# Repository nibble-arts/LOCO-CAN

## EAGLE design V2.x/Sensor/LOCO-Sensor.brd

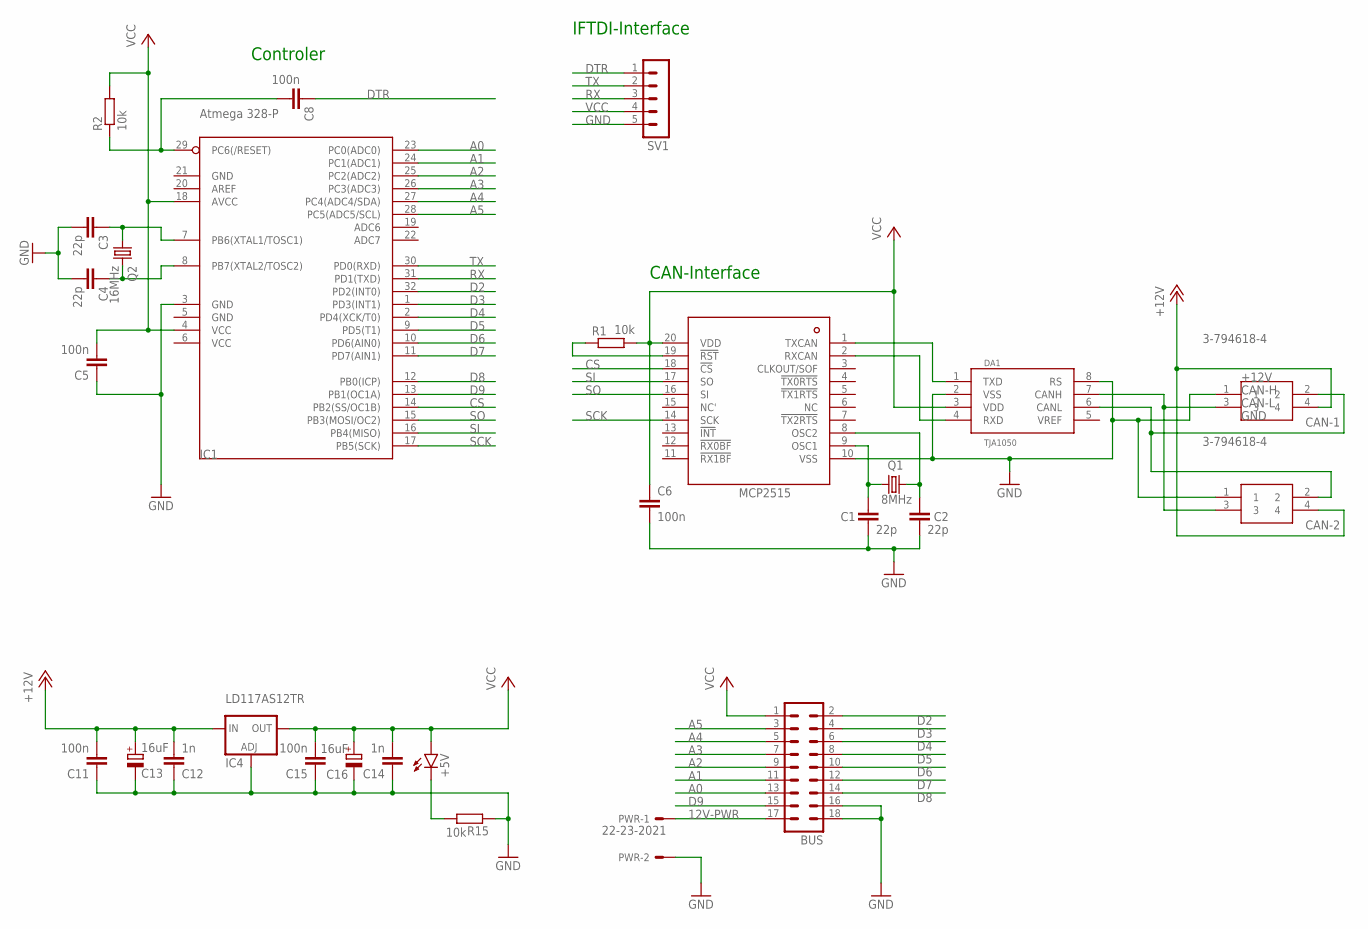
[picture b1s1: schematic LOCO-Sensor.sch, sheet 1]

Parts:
+5V: LEDCHIP-LED0603; CHIP-LED0603
BUS: MA09-2
C1, C2, C3, C4: 22p; C0402K
C5, C6, C8, C11, C15: 100n; C0402K
C12, C14: 1n; C0402K
C13, C16: 16uF; A/3216-18W
CAN-1, CAN-2: 3-794618-4; SHDRRA4W102P300_2X2_686X892X73
DA1: TJA1050; SO08
IC1: Atmega 328-P; TQFP32-08
IC2: MCP2515; TSSOP20
IC4: LD117AS12TR; SOT223
PWR: 22-23-2021
Q1: 8MHz; HC49/S
Q2: 16MHz; HC49/S
R1, R2, R15: 10k; MINI_MELF-0102W
SV1: MA05-1

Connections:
12V-PWR: BUS.17, PWR.1
+12V: C11.2, C12.2, C13.+, CAN-1.4, CAN-2.4, IC4.3 (IN)
A0: BUS.13, IC1.23 (PC0(ADC0))
A1: BUS.11, IC1.24 (PC1(ADC1))
A2: BUS.9, IC1.25 (PC2(ADC2))
A3: BUS.7, IC1.26 (PC3(ADC3))
A4: BUS.5, IC1.27 (PC4(ADC4/SDA))
A5: BUS.3, IC1.28 (PC5(ADC5/SCL))
CAN-H: CAN-1.3, CAN-2.3, DA1.7 (CANH)
CAN-L: CAN-1.2, CAN-2.2, DA1.6 (CANL)
CAN-OCC1: C1.1, IC2.9 (OSC1), Q1.1
CAN-OCC2: C2.1, IC2.8 (OSC2), Q1.2
CS: IC1.14 (PB2(SS/OC1B)), IC2.18 (!CS)
D2: BUS.2, IC1.32 (PD2(INT0))
D3: BUS.4, IC1.1 (PD3(INT1))
D4: BUS.6, IC1.2 (PD4(XCK/T0))
D5: BUS.8, IC1.9 (PD5(T1))
D6: BUS.10, IC1.10 (PD6(AIN0))
D7: BUS.12, IC1.11 (PD7(AIN1))
D8: BUS.14, IC1.12 (PB0(ICP))
D9: BUS.15, IC1.13 (PB1(OC1A))
DTR: C8.1, SV1.1
GND: BUS.16, BUS.18, C1.2, C2.2, C3.2, C4.2, C5.1, C6.2, C11.1, C12.1, C13.-, C14.1, C15.1, C16.-, CAN-1.1, CAN-2.1, DA1.2 (VSS), DA1.8 (RS), IC1.3 (GND), IC1.5 (GND), IC1.21 (GND), IC2.10 (VSS), IC4.1 (ADJ), PWR.2, R15.1, SV1.5
unnamed: IC2.19 (!RST), R1.1
unnamed: C3.1, IC1.7 (PB6(XTAL1/TOSC1)), Q2.1
unnamed: C4.1, IC1.8 (PB7(XTAL2/TOSC2)), Q2.2
unnamed: +5V.C, R15.2
unnamed: C8.2, IC1.29 (PC6(/RESET)), R2.1
RX: IC1.31 (PD1(TXD)), SV1.3
RXCAN: DA1.4 (RXD), IC2.2 (RXCAN)
SCK: IC1.17 (PB5(SCK)), IC2.14 (SCK)
SI: IC1.16 (PB4(MISO)), IC2.17 (SO)
SO: IC1.15 (PB3(MOSI/OC2)), IC2.16 (SI)
TX: IC1.30 (PD0(RXD)), SV1.2
TXCAN: DA1.1 (TXD), IC2.1 (TXCAN)
VCC: +5V.A, BUS.1, C5.2, C6.1, C14.2, C15.2, C16.+, DA1.3 (VDD), IC1.4 (VCC), IC1.6 (VCC), IC1.18 (AVCC), IC2.20 (VDD), IC4.4 (OUT), R1.2, R2.2, SV1.4

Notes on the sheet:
IFTDI-Interface
CAN-Interface
Controler

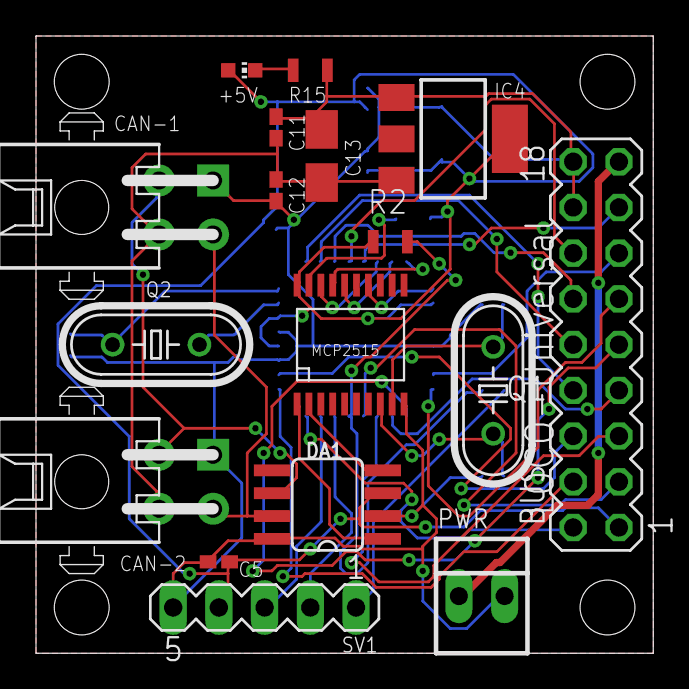
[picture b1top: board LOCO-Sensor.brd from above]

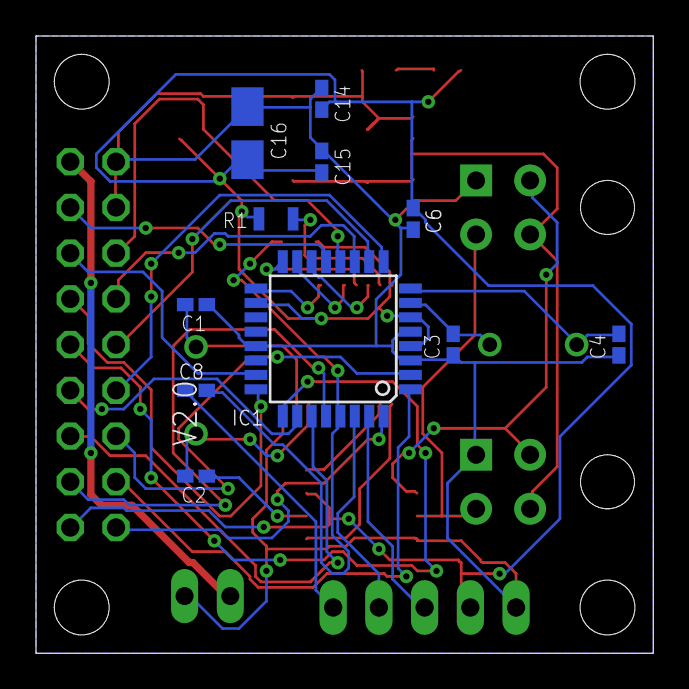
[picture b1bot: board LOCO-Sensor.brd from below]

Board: 2 copper layers, 34.3 x 34.3 mm, 28 parts (11 on the bottom side), 36 nets.

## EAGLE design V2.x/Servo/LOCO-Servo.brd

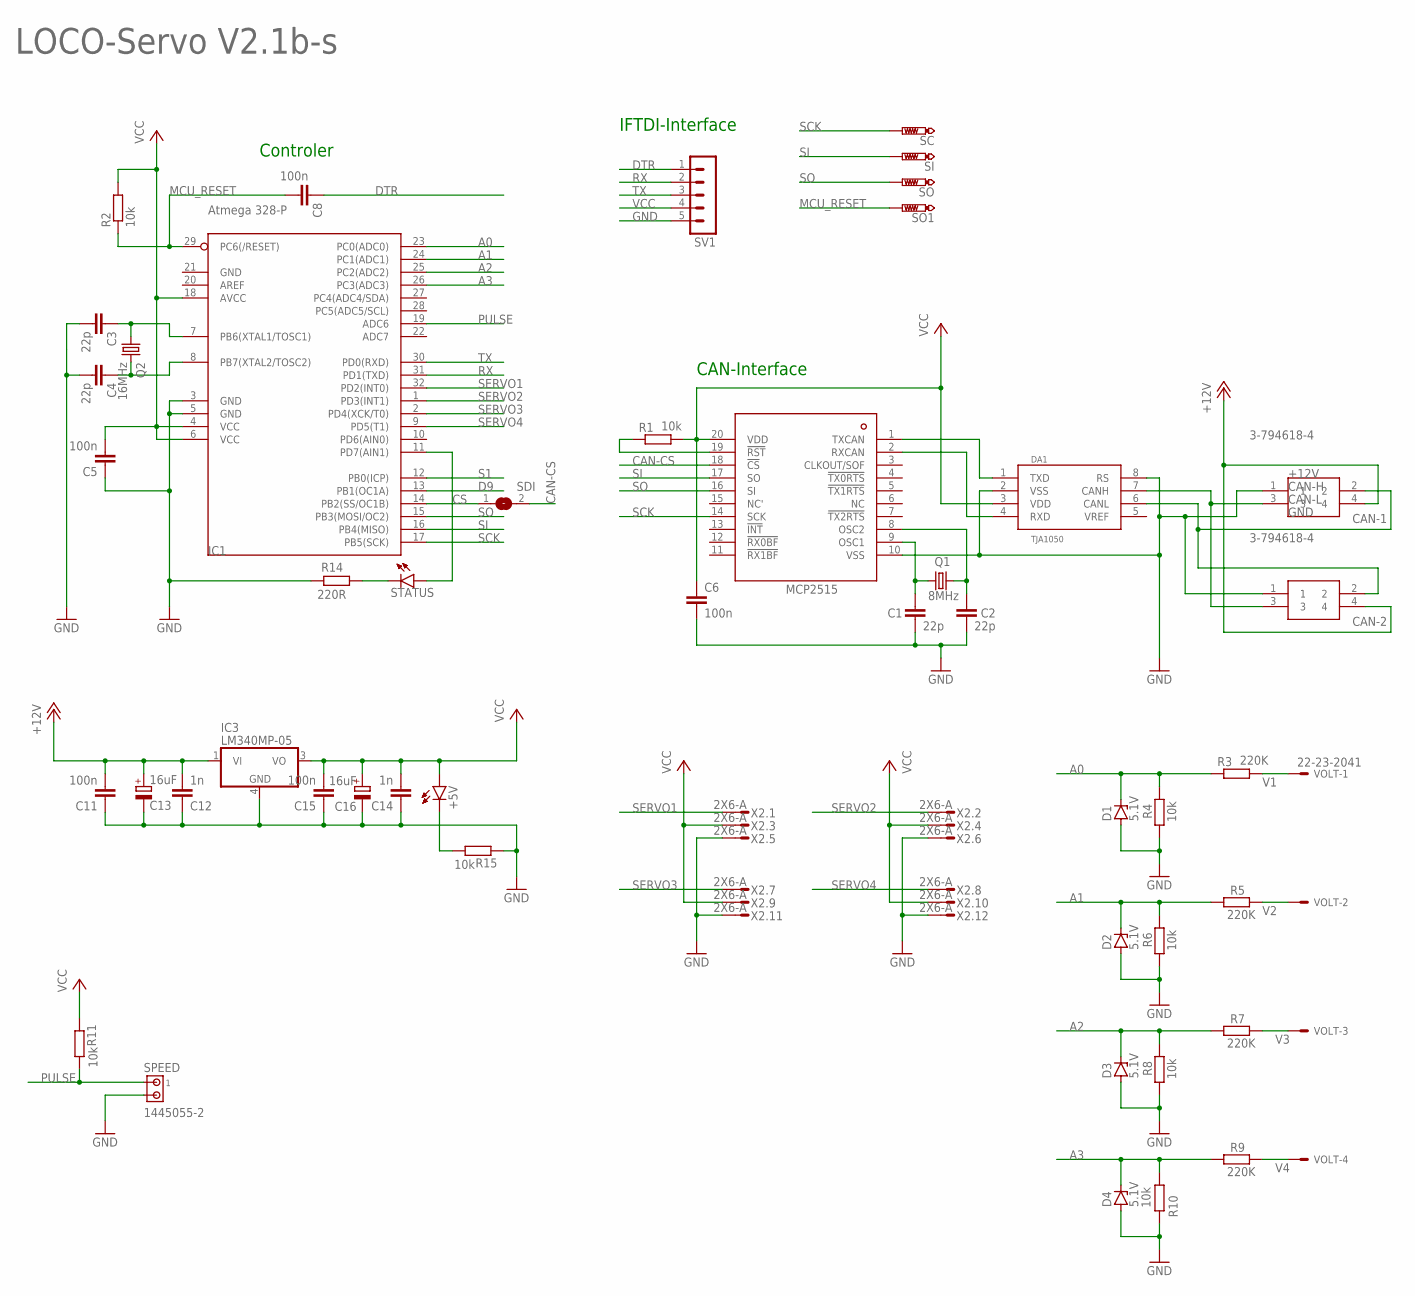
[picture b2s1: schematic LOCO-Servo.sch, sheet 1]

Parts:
+5V: LED_GREEN; LEDC1608X39N_G
C1, C2, C3, C4: 22p; C0402K
C5, C6, C8, C11, C15: 100n; C0402K
C12, C14: 1n; C0402K
C13, C16: 16uF; A/3216-18W
CAN: STATUS; LEDC1608X39N_B
CAN-1, CAN-2: 3-794618-4; SHDRRA4W102P300_2X2_686X892X73
D1, D2, D3, D4: 5.1V; SOD80C
DA1: TJA1050; SO08
IC1: Atmega 328-P; TQFP32-08
IC2: MCP2515; TSSOP20
IC3: LM340MP-05; SOT223
Q1: 8MHz; HC49/S
Q2: 16MHz; HC49/S
R1, R2, R4, R6, R8, R10, R11, R15: 10k; MINI_MELF-0102W
R3, R5, R7, R9: 220K; MINI_MELF-0102W
R14: 220R; MINI_MELF-0102W
SC: PTR1B1,27; B1,27
SDI: SJ
SI: PTR1B1,27; B1,27
SO, SO1: PTR1B1,27; B1,27
SPEED: 1445055-2
SV1: MA05-1
VOLT: 22-23-2041
X2: 2X6-A; 4-794618-2

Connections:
+12V: C11.2, C12.2, C13.+, CAN-1.4, CAN-2.4, IC3.1 (VI)
A0: D1.C, IC1.23 (PC0(ADC0)), R3.1, R4.2
A1: D2.C, IC1.24 (PC1(ADC1)), R5.1, R6.2
A2: D3.C, IC1.25 (PC2(ADC2)), R7.1, R8.2
A3: D4.C, IC1.26 (PC3(ADC3)), R9.1, R10.2
CAN-CS: IC2.18 (!CS), SDI.2
CAN-H: CAN-1.3, CAN-2.3, DA1.7 (CANH)
CAN-L: CAN-1.2, CAN-2.2, DA1.6 (CANL)
CAN-OCC1: C1.1, IC2.9 (OSC1), Q1.1
CAN-OCC2: C2.1, IC2.8 (OSC2), Q1.2
CS: IC1.14 (PB2(SS/OC1B)), SDI.1
D9: IC1.13 (PB1(OC1A))
DTR: C8.1, SV1.1
GND: C1.2, C2.2, C3.2, C4.2, C5.1, C6.2, C11.1, C12.1, C13.-, C14.1, C15.1, C16.-, CAN-1.1, CAN-2.1, D1.A, D2.A, D3.A, D4.A, DA1.2 (VSS), DA1.8 (RS), IC1.3 (GND), IC1.5 (GND), IC1.21 (GND), IC2.10 (VSS), IC3.4 (GND), R4.1, R6.1, R8.1, R10.1, R14.2, R15.1, SPEED.2, SV1.5, X2.5, X2.6, X2.11, X2.12
MCU_RESET: C8.2, IC1.29 (PC6(/RESET)), R2.1, SO1.TP
unnamed: CAN.1 (C), R14.1
unnamed: CAN.2 (A), IC1.11 (PD7(AIN1))
unnamed: IC2.19 (!RST), R1.1
unnamed: C3.1, IC1.7 (PB6(XTAL1/TOSC1)), Q2.1
unnamed: C4.1, IC1.8 (PB7(XTAL2/TOSC2)), Q2.2
unnamed: +5V.1 (C), R15.2
PULSE: IC1.19 (ADC6), R11.2, SPEED.1
RX: IC1.31 (PD1(TXD)), SV1.2
RXCAN: DA1.4 (RXD), IC2.2 (RXCAN)
S1: IC1.12 (PB0(ICP))
SCK: IC1.17 (PB5(SCK)), IC2.14 (SCK), SC.TP
SERVO1: IC1.32 (PD2(INT0)), X2.1
SERVO2: IC1.1 (PD3(INT1)), X2.2
SERVO3: IC1.2 (PD4(XCK/T0)), X2.7
SERVO4: IC1.9 (PD5(T1)), X2.8
SI: IC1.16 (PB4(MISO)), IC2.17 (SO), SI.TP
SO: IC1.15 (PB3(MOSI/OC2)), IC2.16 (SI), SO.TP
TX: IC1.30 (PD0(RXD)), SV1.3
TXCAN: DA1.1 (TXD), IC2.1 (TXCAN)
V1: R3.2, VOLT.1
V2: R5.2, VOLT.2
V3: R7.2, VOLT.3
V4: R9.2, VOLT.4
VCC: +5V.2 (A), C5.2, C6.1, C14.2, C15.2, C16.+, DA1.3 (VDD), IC1.4 (VCC), IC1.6 (VCC), IC1.18 (AVCC), IC2.20 (VDD), IC3.3 (VO), R1.2, R2.2, R11.1, SV1.4, X2.3, X2.4, X2.9, X2.10

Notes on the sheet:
IFTDI-Interface
CAN-Interface
Controler
LOCO-Servo V2.1b-s

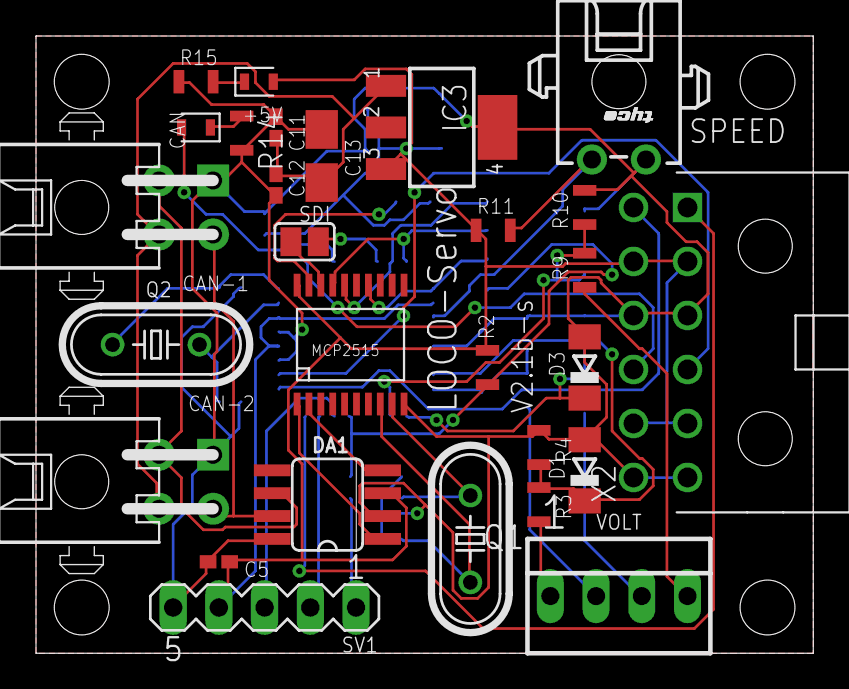
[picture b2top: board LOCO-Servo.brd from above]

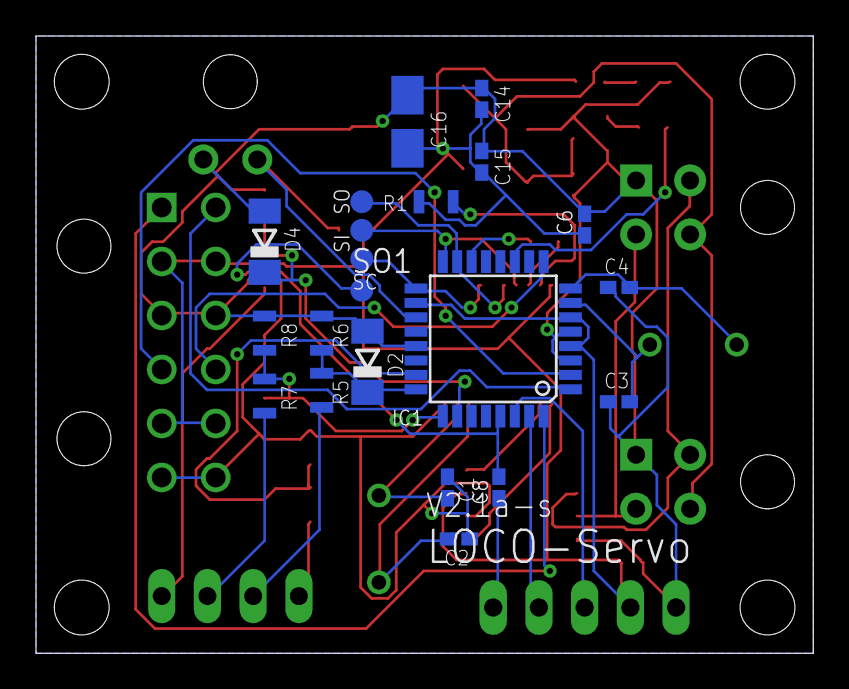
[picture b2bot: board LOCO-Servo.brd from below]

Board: 2 copper layers, 43.2 x 34.3 mm, 49 parts (21 on the bottom side), 37 nets.

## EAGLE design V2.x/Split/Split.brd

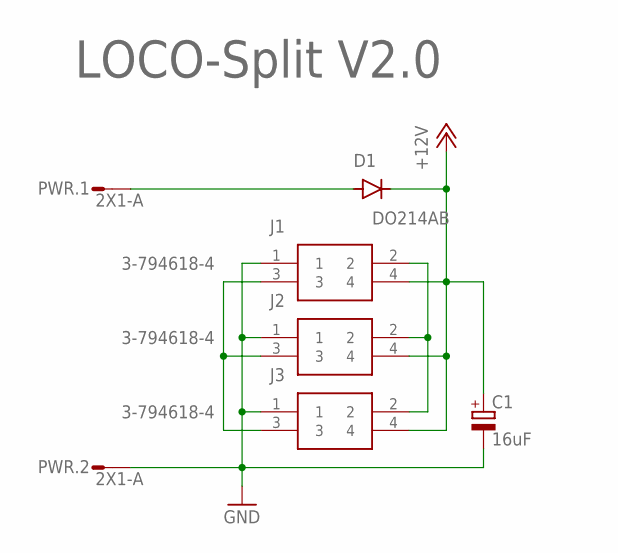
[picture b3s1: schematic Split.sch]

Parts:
C1: 16uF; A/3216-18W
D1: DO214AB; DO214AC
J1, J2, J3: 3-794618-4; SHDRRA4W102P300_2X2_686X892X73
PWR: 2X1-A; 3-794618-2

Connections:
+12V: C1.+, D1.C, J1.4, J2.4, J3.4
GND: C1.-, J1.1, J2.1, J3.1, PWR.2
unnamed: D1.A, PWR.1
unnamed: J1.3, J2.3, J3.3
unnamed: J1.2, J2.2, J3.2

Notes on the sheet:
LOCO-Split V2.0

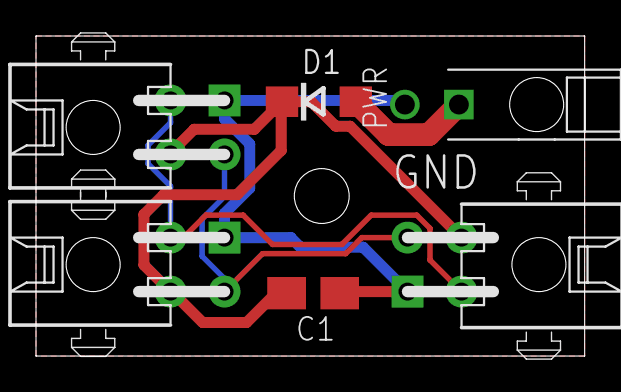
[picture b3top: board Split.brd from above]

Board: 2 copper layers, 30.5 x 17.8 mm, 6 parts (0 on the bottom side), 5 nets.

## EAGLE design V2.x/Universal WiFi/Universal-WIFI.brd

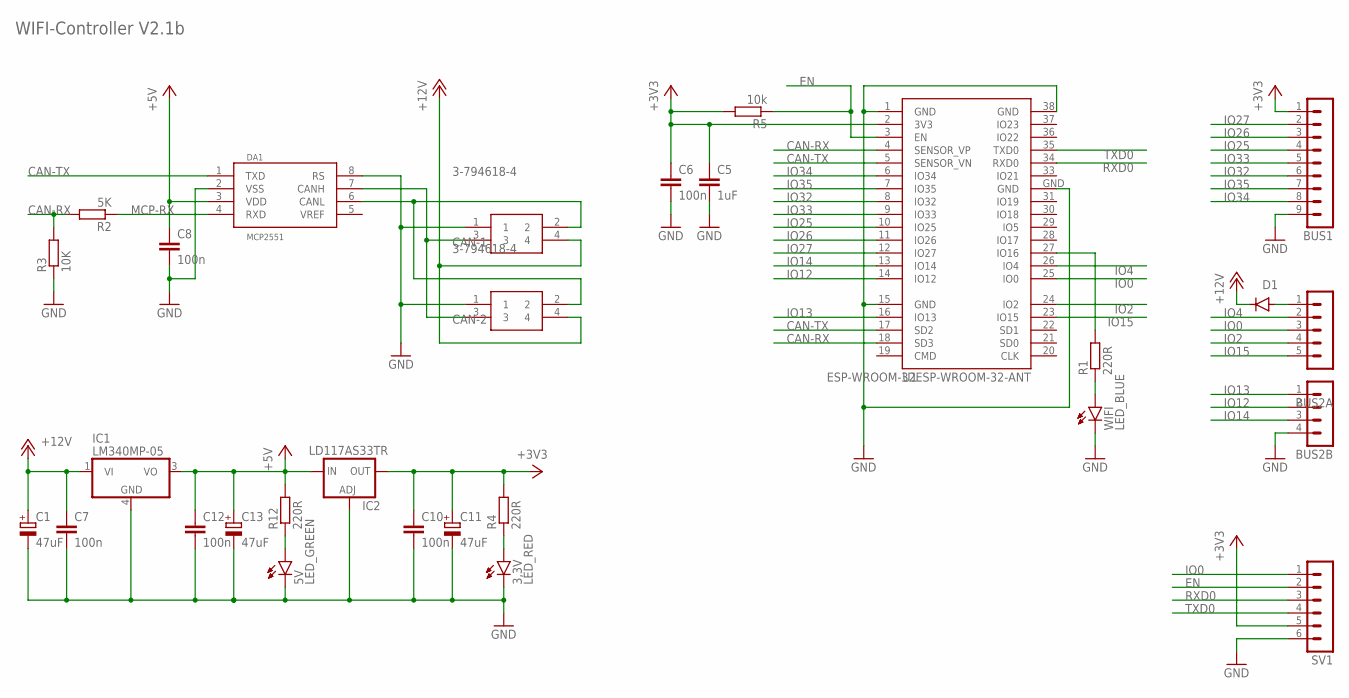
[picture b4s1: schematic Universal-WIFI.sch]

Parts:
3,3V: LED_RED; LEDC1608X39N_R
5V: LED_GREEN; LEDC1608X39N_G
BUS1: MA09-1
BUS2A: MA05-1
BUS2B: MA04-1
C1, C11, C13: 47uF; B/3528-21R
C5: 1uF; C0402
C6, C7, C8, C10, C12: 100n; C0402
CAN-1, CAN-2: 3-794618-4; SHDRRA4W102P300_2X2_686X892X73
D1: DIODE-DO-214AC; DO-214AC
DA1: MCP2551; SO08
IC1: LM340MP-05; SOT223
IC2: LD117AS33TR; SOT223
R1, R4, R12: 220R; R0805
R2: 5K; R0805
R3: 10K; R0805
R5: 10k; R0805
SV1: MA06-1
U1: ESP-WROOM-32ESP-WROOM-32-ANT; ESP-WROOM-32-ANT
WIFI: LED_BLUE; LEDC1608X39N_B

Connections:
+3V3: BUS1.1, C5.1, C6.1, C10.1, C11.+, IC2.4 (OUT), R4.2, R5.2, SV1.5, U1.2 (3V3)
+5V: C8.1, C12.1, C13.+, DA1.3 (VDD), IC1.3 (VO), IC2.3 (IN), R12.2
+12V: C1.+, C7.1, CAN-1.4, CAN-2.4, D1.C, IC1.1 (VI)
CAN-RX: R2.2, R3.2, U1.4 (SENSOR_VP), U1.18 (SD3)
CAN-TX: DA1.1 (TXD), U1.5 (SENSOR_VN), U1.17 (SD2)
EN: R5.1, SV1.2, U1.3 (EN)
GND: 3,3V.1 (C), 5V.1 (C), BUS1.9, BUS2B.4, C1.-, C5.2, C6.2, C7.2, C8.2, C10.2, C11.-, C12.2, C13.-, CAN-1.1, CAN-2.1, DA1.2 (VSS), DA1.8 (RS), IC1.4 (GND), IC2.1 (ADJ), R3.1, SV1.6, U1.1 (GND), U1.15 (GND), U1.38 (GND), U1.GND, WIFI.1 (C)
IO0: BUS2A.3, SV1.1, U1.25 (IO0)
IO2: BUS2A.4, U1.24 (IO2)
IO4: BUS2A.2, U1.26 (IO4)
IO12: BUS2B.2, U1.14 (IO12)
IO13: BUS2B.1, U1.16 (IO13)
IO14: BUS2B.3, U1.13 (IO14)
IO15: BUS2A.5, U1.23 (IO15)
IO25: BUS1.4, U1.10 (IO25)
IO26: BUS1.3, U1.11 (IO26)
IO27: BUS1.2, U1.12 (IO27)
IO32: BUS1.6, U1.8 (IO32)
IO33: BUS1.5, U1.9 (IO33)
IO34: BUS1.8, U1.6 (IO34)
IO35: BUS1.7, U1.7 (IO35)
MCP-RX: DA1.4 (RXD), R2.1
unnamed: BUS2A.1, D1.A
unnamed: R1.2, U1.27 (IO16)
unnamed: R1.1, WIFI.2 (A)
unnamed: 3,3V.2 (A), R4.1
unnamed: CAN-1.3, CAN-2.3, DA1.7 (CANH)
unnamed: CAN-1.2, CAN-2.2, DA1.6 (CANL)
unnamed: 5V.2 (A), R12.1
RXD0: SV1.3, U1.34 (RXD0)
TXD0: SV1.4, U1.35 (TXD0)

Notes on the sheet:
WIFI-Controller V2.1b

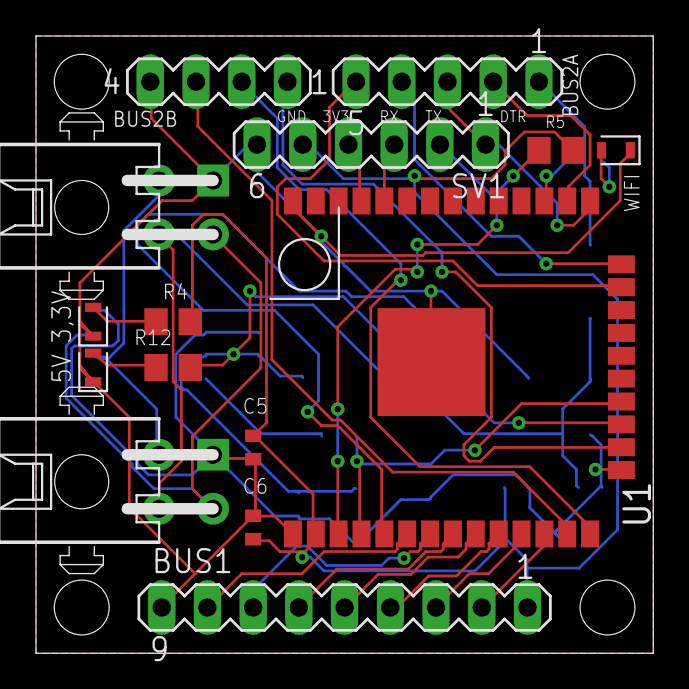
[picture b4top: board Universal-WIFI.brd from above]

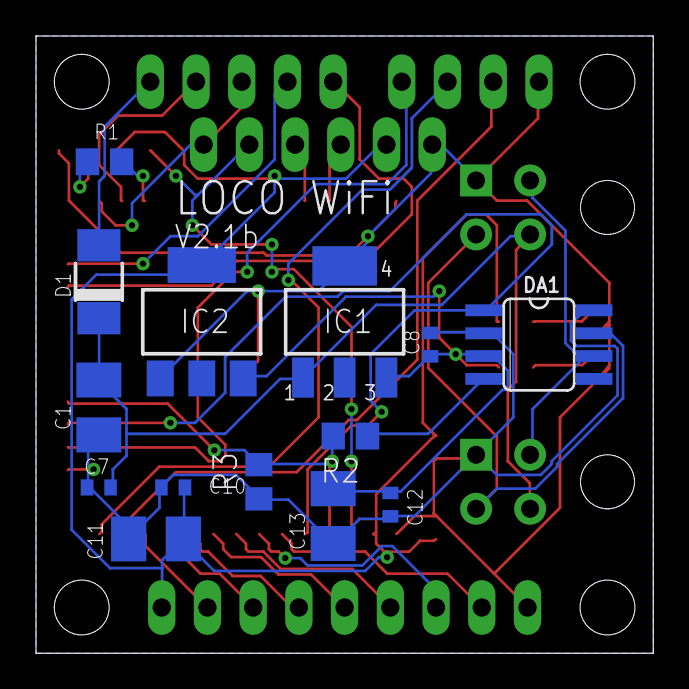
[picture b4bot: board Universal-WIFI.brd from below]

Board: 2 copper layers, 34.3 x 34.3 mm, 29 parts (14 on the bottom side), 31 nets.

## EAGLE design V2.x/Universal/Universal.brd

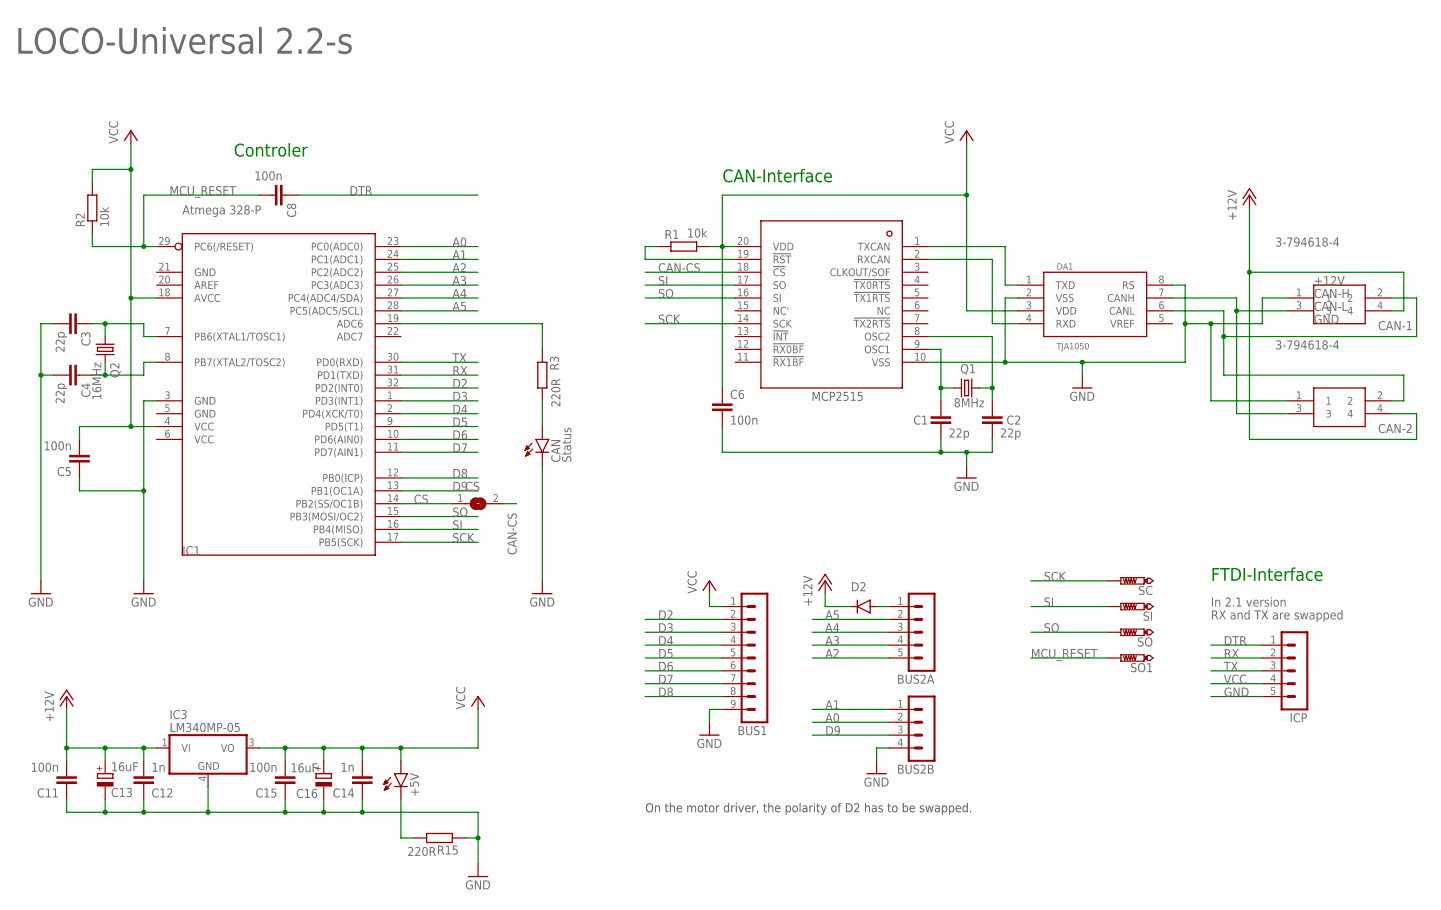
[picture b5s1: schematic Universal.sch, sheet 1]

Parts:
+5V: LEDCHIP-LED0603; CHIP-LED0603
BUS1: MA09-1
BUS2A: MA05-1
BUS2B: MA04-1
C1, C2, C3, C4: 22p; C0402K
C5, C6, C8, C11, C15: 100n; C0402K
C12, C14: 1n; C0402K
C13, C16: 16uF; A/3216-18W
CAN: Status; SML0603
CAN-1, CAN-2: 3-794618-4; SHDRRA4W102P300_2X2_686X892X73
CS: SJ
D2: DIODE-DO214AA; DO214AA
DA1: TJA1050; SO08
IC1: Atmega 328-P; TQFP32-08
IC2: MCP2515; TSSOP20
IC3: LM340MP-05; SOT223
ICP: MA05-1
Q1: 8MHz; HC49/S
Q2: 16MHz; HC49/S
R1, R2: 10k; MINI_MELF-0102W
R3, R15: 220R; MINI_MELF-0102W
SC: PTR1B1,27; B1,27
SI: PTR1B1,27; B1,27
SO, SO1: PTR1B1,27; B1,27

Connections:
+12V: C11.2, C12.2, C13.+, CAN-1.4, CAN-2.4, D2.C, IC3.1 (VI)
A0: BUS2B.2, IC1.23 (PC0(ADC0))
A1: BUS2B.1, IC1.24 (PC1(ADC1))
A2: BUS2A.5, IC1.25 (PC2(ADC2))
A3: BUS2A.4, IC1.26 (PC3(ADC3))
A4: BUS2A.3, IC1.27 (PC4(ADC4/SDA))
A5: BUS2A.2, IC1.28 (PC5(ADC5/SCL))
CAN-CS: CS.2, IC2.18 (!CS)
CAN-H: CAN-1.3, CAN-2.3, DA1.7 (CANH)
CAN-L: CAN-1.2, CAN-2.2, DA1.6 (CANL)
CAN-OCC1: C1.1, IC2.9 (OSC1), Q1.1
CAN-OCC2: C2.1, IC2.8 (OSC2), Q1.2
CS: CS.1, IC1.14 (PB2(SS/OC1B))
D2: BUS1.2, IC1.32 (PD2(INT0))
D3: BUS1.3, IC1.1 (PD3(INT1))
D4: BUS1.4, IC1.2 (PD4(XCK/T0))
D5: BUS1.5, IC1.9 (PD5(T1))
D6: BUS1.6, IC1.10 (PD6(AIN0))
D7: BUS1.7, IC1.11 (PD7(AIN1))
D8: BUS1.8, IC1.12 (PB0(ICP))
D9: BUS2B.3, IC1.13 (PB1(OC1A))
DTR: C8.1, ICP.1
GND: BUS1.9, BUS2B.4, C1.2, C2.2, C3.2, C4.2, C5.1, C6.2, C11.1, C12.1, C13.-, C14.1, C15.1, C16.-, CAN.C, CAN-1.1, CAN-2.1, DA1.2 (VSS), DA1.8 (RS), IC1.3 (GND), IC1.5 (GND), IC1.21 (GND), IC2.10 (VSS), IC3.4 (GND), ICP.5, R15.1
MCU_RESET: C8.2, IC1.29 (PC6(/RESET)), R2.1, SO1.TP
unnamed: IC1.19 (ADC6), R3.1
unnamed: BUS2A.1, D2.A
unnamed: CAN.A, R3.2
unnamed: IC2.19 (!RST), R1.1
unnamed: C3.1, IC1.7 (PB6(XTAL1/TOSC1)), Q2.1
unnamed: C4.1, IC1.8 (PB7(XTAL2/TOSC2)), Q2.2
unnamed: +5V.C, R15.2
RX: IC1.31 (PD1(TXD)), ICP.2
RXCAN: DA1.4 (RXD), IC2.2 (RXCAN)
SCK: IC1.17 (PB5(SCK)), IC2.14 (SCK), SC.TP
SI: IC1.16 (PB4(MISO)), IC2.17 (SO), SI.TP
SO: IC1.15 (PB3(MOSI/OC2)), IC2.16 (SI), SO.TP
TX: IC1.30 (PD0(RXD)), ICP.3
TXCAN: DA1.1 (TXD), IC2.1 (TXCAN)
VCC: +5V.A, BUS1.1, C5.2, C6.1, C14.2, C15.2, C16.+, DA1.3 (VDD), IC1.4 (VCC), IC1.6 (VCC), IC1.18 (AVCC), IC2.20 (VDD), IC3.3 (VO), ICP.4, R1.2, R2.2

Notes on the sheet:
FTDI-Interface
CAN-Interface
Controler
LOCO-Universal 2.2-s
RX and TX are swapped
In 2.1 version
On the motor driver, the polarity of D2 has to be swapped.

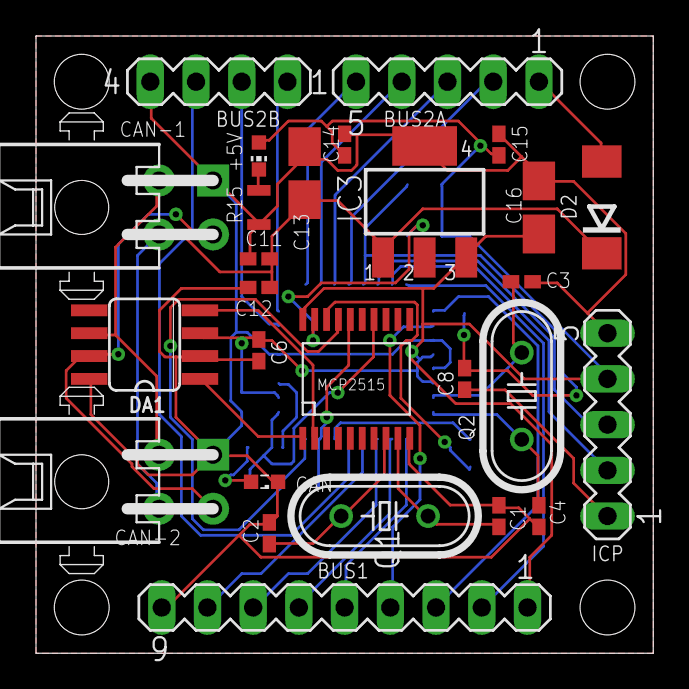
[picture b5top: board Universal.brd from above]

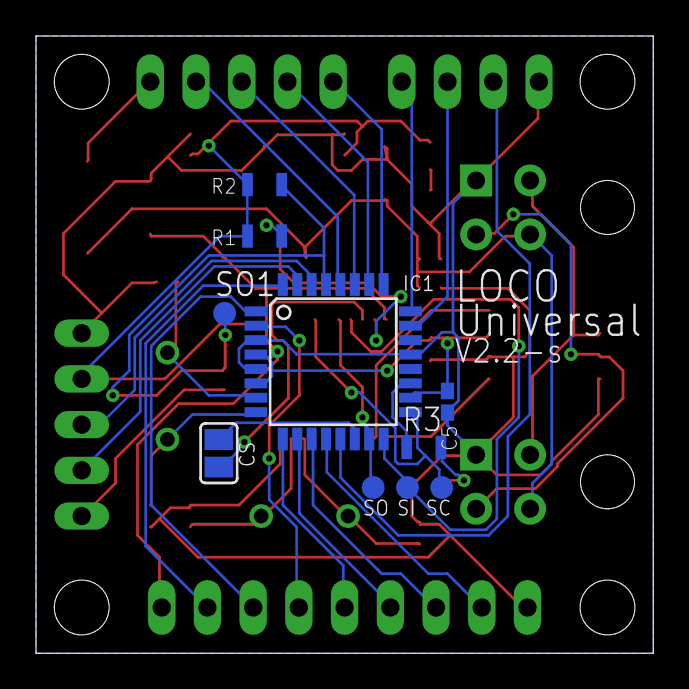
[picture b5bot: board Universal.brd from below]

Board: 2 copper layers, 34.3 x 34.3 mm, 37 parts (10 on the bottom side), 39 nets.

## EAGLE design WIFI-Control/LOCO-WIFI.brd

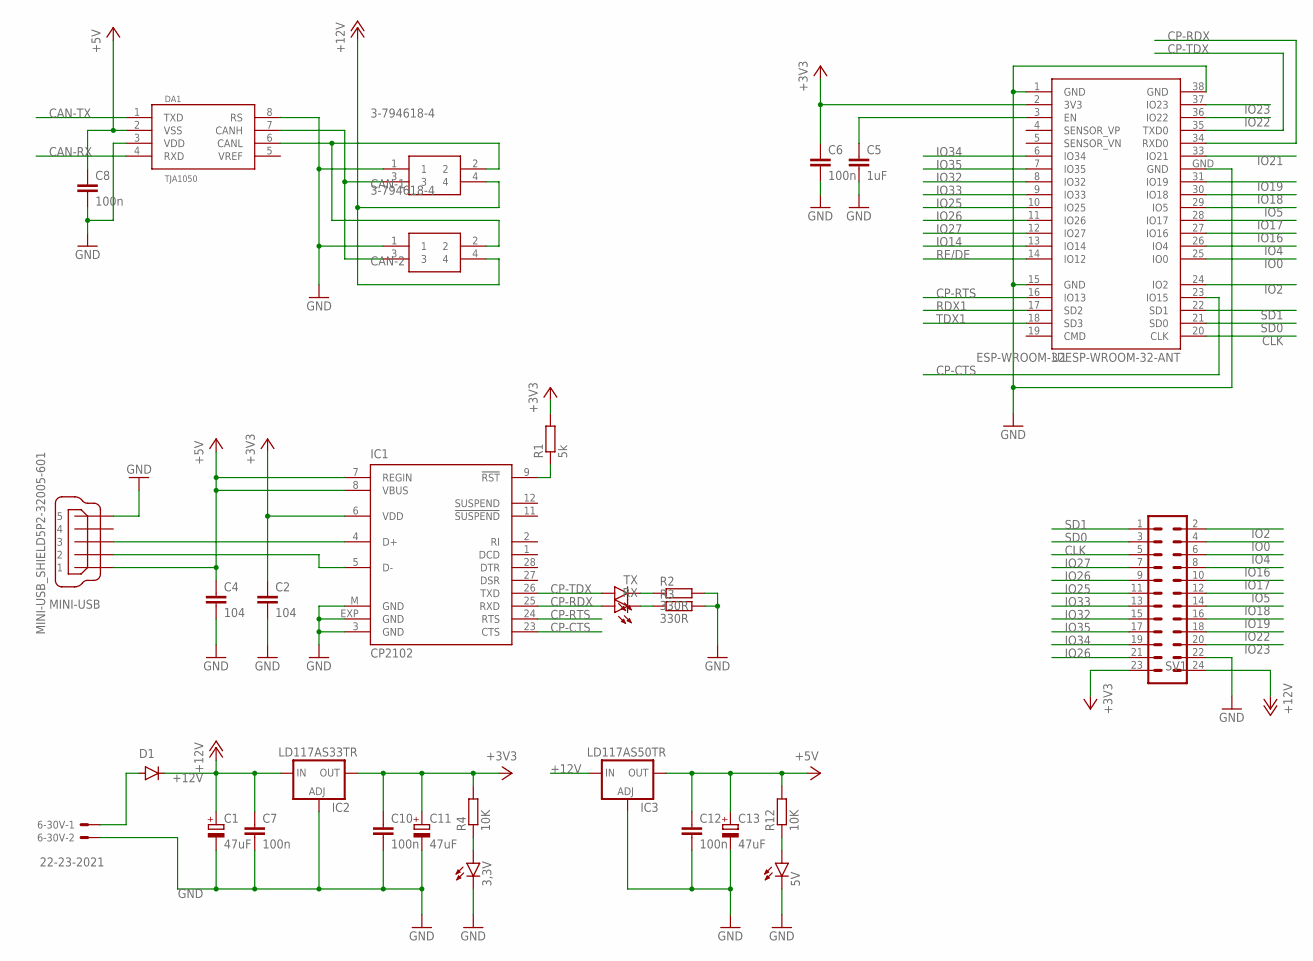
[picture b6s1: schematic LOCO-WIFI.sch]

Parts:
3,3V, 5V: LEDCHIPLED_0603; CHIPLED_0603
6-30V: 22-23-2021
C1, C11, C13: 47uF; B/3528-21R
C2, C4: 104; C0402
C5: 1uF; C0402
C6, C7, C8, C10, C12: 100n; C0402
CAN-1, CAN-2: 3-794618-4; SHDRRA4W102P300_2X2_686X892X73
D1: DIODE-DO-214AC; DO-214AC
DA1: TJA1050; SO08
IC1: CP2102; MLP28
IC2: LD117AS33TR; SOT223
IC3: LD117AS50TR; SOT223
MINI-USB: MINI-USB_SHIELD5P2-32005-601; 32005-601
R1: 5k; R0603
R2, R3: 330R; R0603
R4, R12: 10K; R0603
RX: LEDCHIPLED_0603; CHIPLED_0603
SV1: MA12-2
TX: LEDCHIPLED_0603; CHIPLED_0603
U1: ESP-WROOM-32ESP-WROOM-32-ANT; ESP-WROOM-32-ANT

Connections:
+3V3: C2.1, C6.1, C10.1, C11.+, IC1.6 (VDD), IC2.4 (OUT), R1.2, R4.2, SV1.23, U1.2 (3V3)
+5V: C4.1, C8.1, C12.1, C13.+, DA1.2 (VSS), IC1.7 (REGIN), IC1.8 (VBUS), IC3.4 (OUT), MINI-USB.1, R12.2
+12V: C1.+, C7.1, CAN-1.4, CAN-2.4, D1.C, IC2.3 (IN), IC3.3 (IN), SV1.24
CAN-RX: DA1.4 (RXD)
CAN-TX: DA1.1 (TXD)
CLK: SV1.5, U1.20 (CLK)
CP-CTS: IC1.23 (CTS), U1.23 (IO15)
CP-RDX: IC1.25 (RXD), RX.A, U1.34 (RXD0)
CP-RTS: IC1.24 (RTS), U1.16 (IO13)
CP-TDX: IC1.26 (TXD), TX.A, U1.35 (TXD0)
GND: 3,3V.C, 5V.C, 6-30V.2, C1.-, C2.2, C4.2, C5.2, C6.2, C7.2, C8.2, C10.2, C11.-, C12.2, C13.-, CAN-1.1, CAN-2.1, DA1.3 (VDD), DA1.8 (RS), IC1.3 (GND), IC1.EXP (GND), IC1.M (GND), IC2.1 (ADJ), IC3.1 (ADJ), MINI-USB.5, R2.2, R3.2, SV1.22, U1.1 (GND), U1.15 (GND), U1.38 (GND), U1.GND
IO0: SV1.4, U1.25 (IO0)
IO2: SV1.2, U1.24 (IO2)
IO4: SV1.6, U1.26 (IO4)
IO5: SV1.12, U1.29 (IO5)
IO14: U1.13 (IO14)
IO16: SV1.8, U1.27 (IO16)
IO17: SV1.10, U1.28 (IO17)
IO18: SV1.14, U1.30 (IO18)
IO19: SV1.16, U1.31 (IO19)
IO21: U1.33 (IO21)
IO22: SV1.18, U1.36 (IO22)
IO23: SV1.20, U1.37 (IO23)
IO25: SV1.11, U1.10 (IO25)
IO26: SV1.9, SV1.21, U1.11 (IO26)
IO27: SV1.7, U1.12 (IO27)
IO32: SV1.15, U1.8 (IO32)
IO33: SV1.13, U1.9 (IO33)
IO34: SV1.19, U1.6 (IO34)
IO35: SV1.17, U1.7 (IO35)
unnamed: IC1.5 (D-), MINI-USB.2
unnamed: IC1.4 (D+), MINI-USB.3
unnamed: IC1.9 (!RST), R1.1
unnamed: 6-30V.1, D1.A
unnamed: R2.1, TX.C
unnamed: 3,3V.A, R4.1
unnamed: R3.1, RX.C
unnamed: CAN-1.3, CAN-2.3, DA1.7 (CANH)
unnamed: CAN-1.2, CAN-2.2, DA1.6 (CANL)
unnamed: 5V.A, R12.1
RDX1: U1.17 (SD2)
RE/DE: U1.14 (IO12)
RESET: C5.1, U1.3 (EN)
SD0: SV1.3, U1.21 (SD0)
SD1: SV1.1, U1.22 (SD1)
TDX1: U1.18 (SD3)

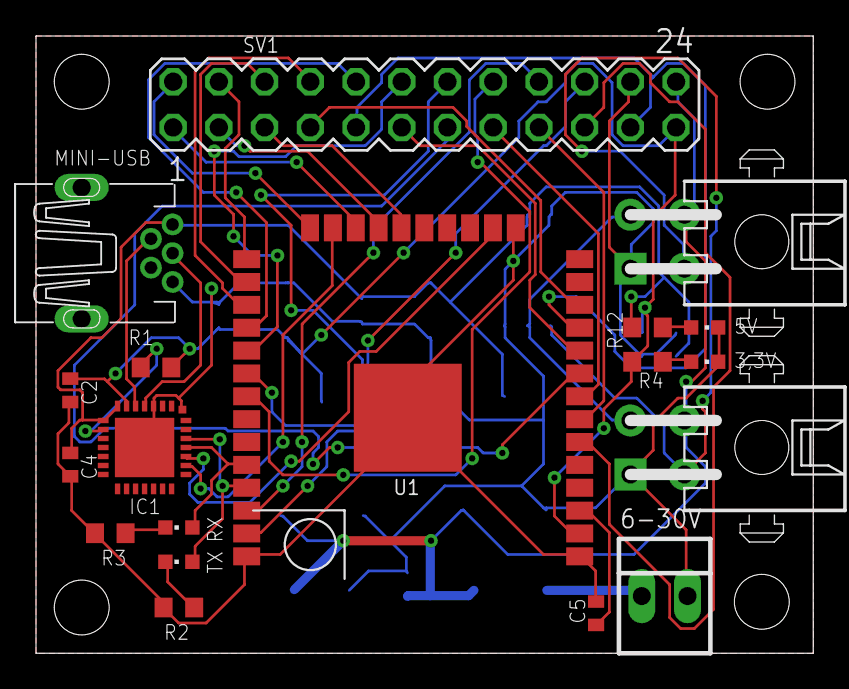
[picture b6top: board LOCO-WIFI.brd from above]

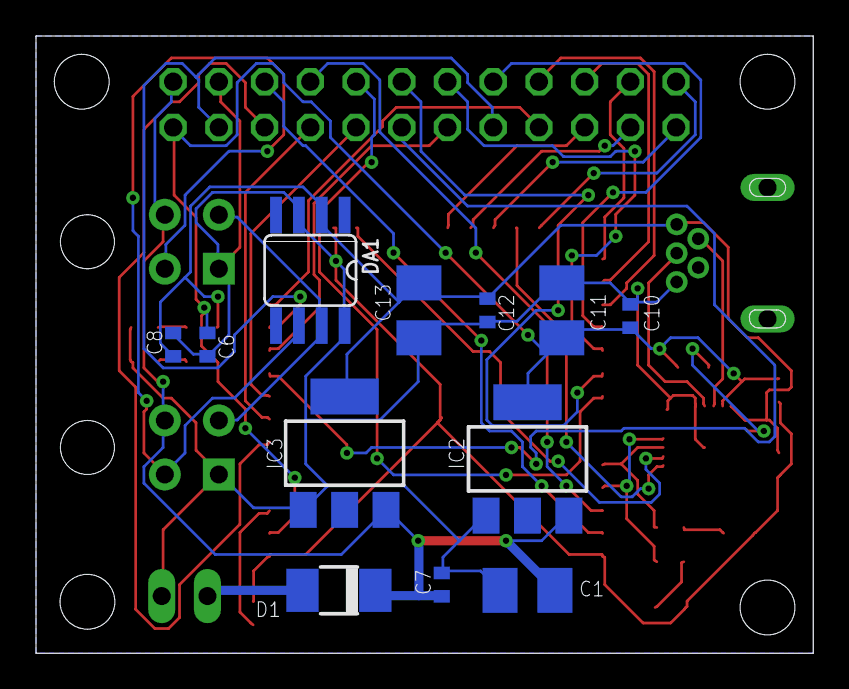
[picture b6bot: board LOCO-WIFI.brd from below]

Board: 2 copper layers, 43.2 x 34.3 mm, 31 parts (12 on the bottom side), 39 nets.

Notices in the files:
parts and their libraries:
esp32: Creative Commons Attribution-ShareAlike 4.0 International
